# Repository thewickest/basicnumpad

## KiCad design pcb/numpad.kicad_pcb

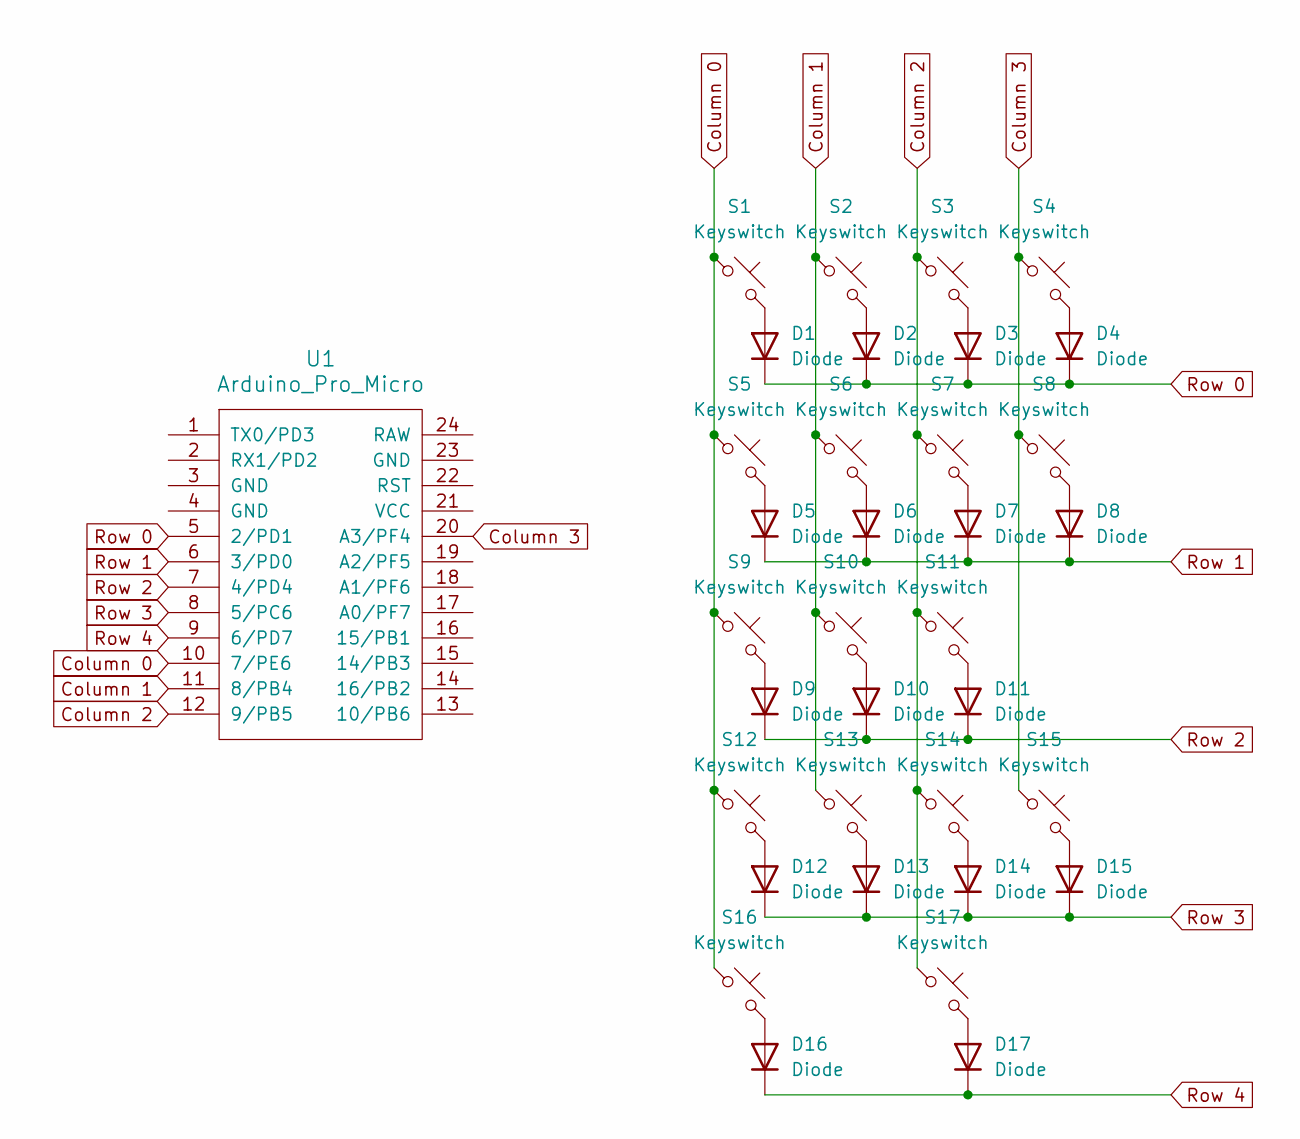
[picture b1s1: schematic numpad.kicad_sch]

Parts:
D1, D2, D3, D4, D5, D6, D7, D8, D9, D10, D11, D12, D13, D14, D15, D16, D17: Diode; Diode_DO-35
S1, S2, S3, S4, S5, S6, S7, S9, S10, S11, S12, S13, S14, S17: Keyswitch; MX_PCB_1.00u
S8, S15: Keyswitch; MX_PCB_2.00u_90deg
S16: Keyswitch; MX_PCB_2.00u
U1: Arduino_Pro_Micro

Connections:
Column 0: S1.1, S5.1, S9.1, S12.1, S16.1, U1.10 (7/PE6)
Column 1: S2.1, S6.1, S10.1, S13.1, U1.11 (8/PB4)
Column 2: S3.1, S7.1, S11.1, S14.1, S17.1, U1.12 (9/PB5)
Column 3: S4.1, S8.1, S15.1, U1.20 (A3/PF4)
unnamed: D1.2 (A), S1.2
unnamed: D2.2 (A), S2.2
unnamed: D3.2 (A), S3.2
unnamed: D4.2 (A), S4.2
unnamed: D5.2 (A), S5.2
unnamed: D6.2 (A), S6.2
unnamed: D7.2 (A), S7.2
unnamed: D8.2 (A), S8.2
unnamed: D9.2 (A), S9.2
unnamed: D10.2 (A), S10.2
unnamed: D11.2 (A), S11.2
unnamed: D12.2 (A), S12.2
unnamed: D13.2 (A), S13.2
unnamed: D14.2 (A), S14.2
unnamed: D15.2 (A), S15.2
unnamed: D16.2 (A), S16.2
unnamed: D17.2 (A), S17.2
Row 0: D1.1 (K), D2.1 (K), D3.1 (K), D4.1 (K), U1.5 (2/PD1)
Row 1: D5.1 (K), D6.1 (K), D7.1 (K), D8.1 (K), U1.6 (3/PD0)
Row 2: D9.1 (K), D10.1 (K), D11.1 (K), U1.7 (4/PD4)
Row 3: D12.1 (K), D13.1 (K), D14.1 (K), D15.1 (K), U1.8 (5/PC6)
Row 4: D16.1 (K), D17.1 (K), U1.9 (6/PD7)

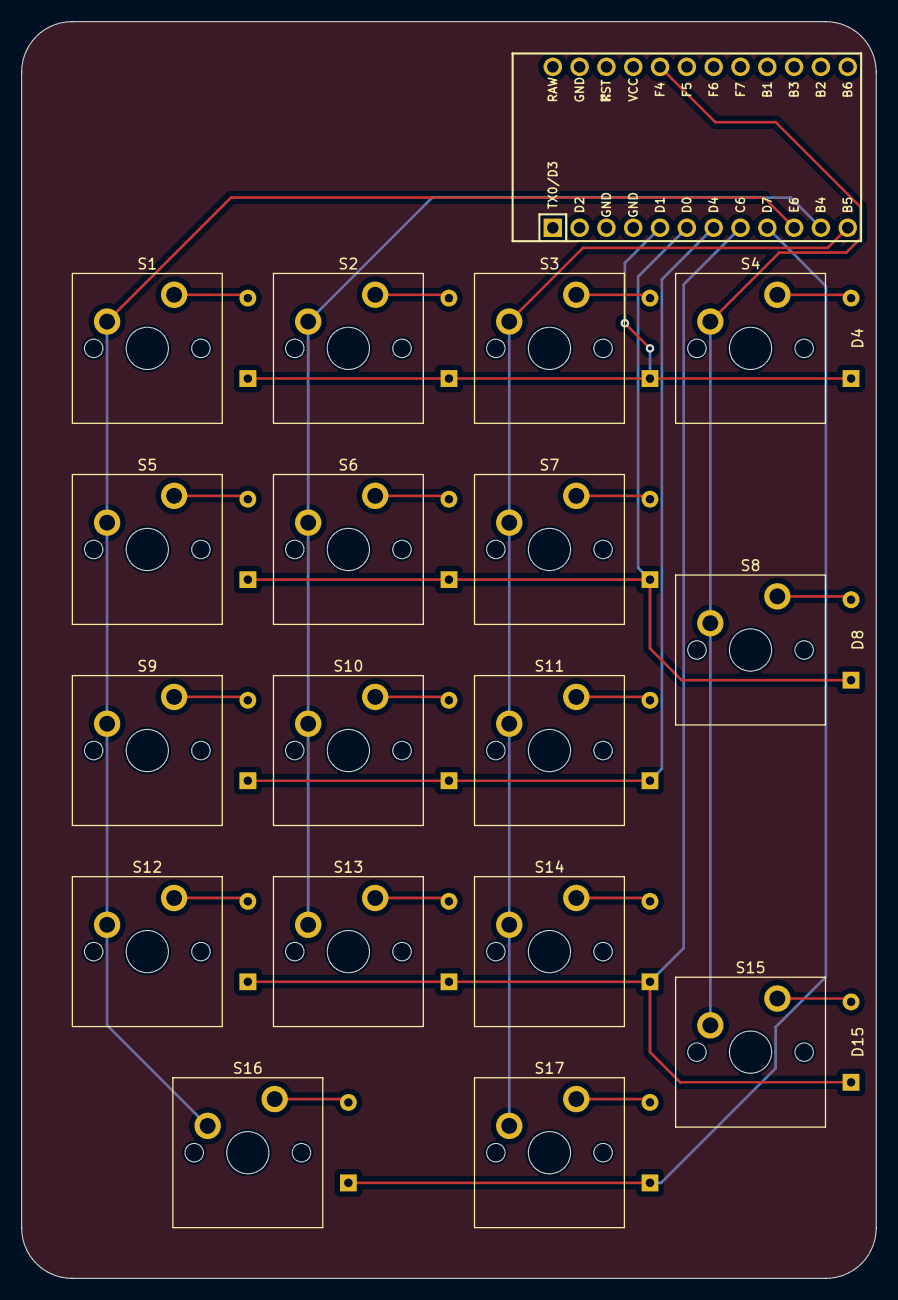
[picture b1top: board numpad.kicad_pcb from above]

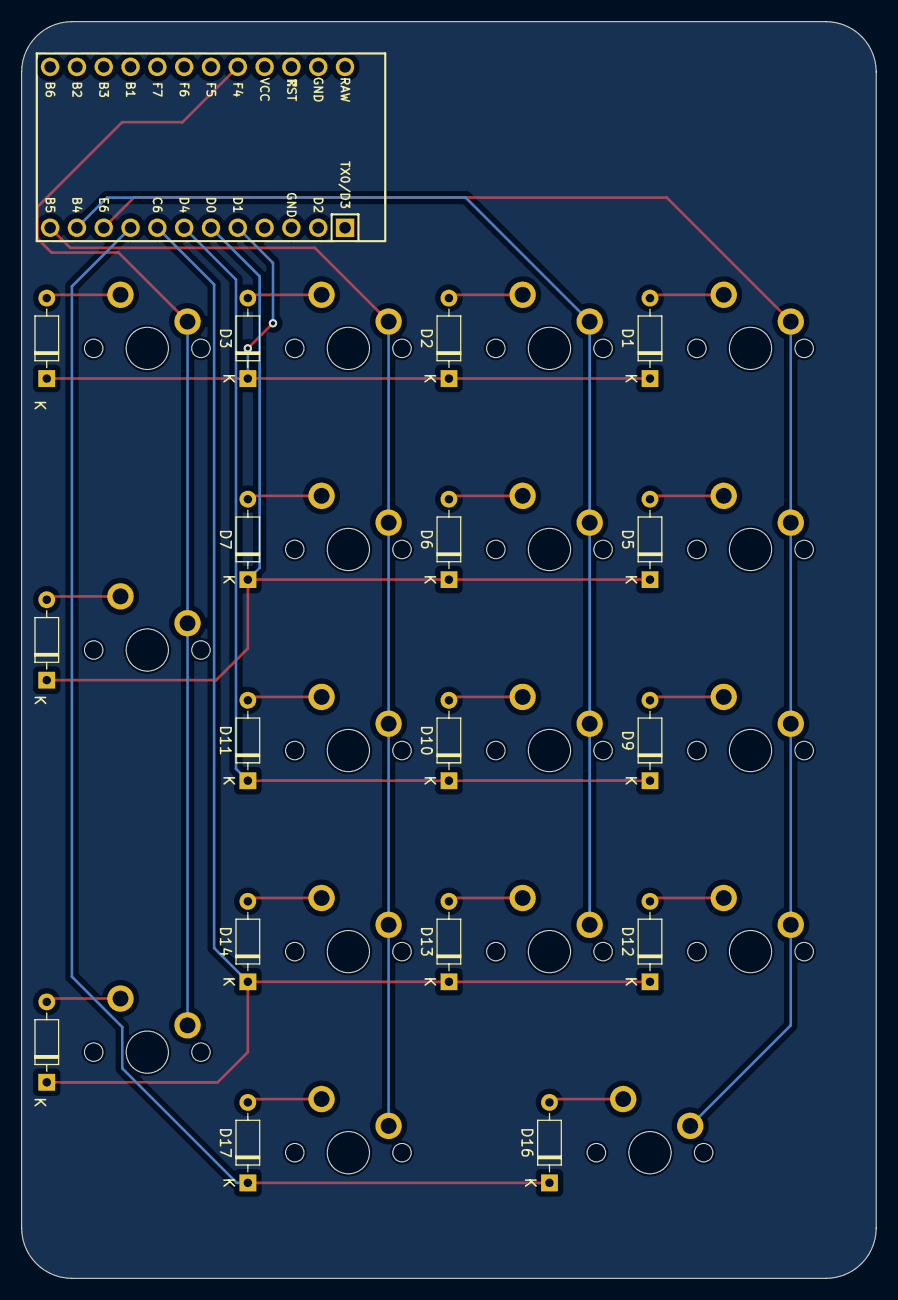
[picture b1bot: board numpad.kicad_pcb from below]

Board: 2 copper layers, 81.0 x 119.1 mm, 35 parts (17 on the bottom side), 26 nets.

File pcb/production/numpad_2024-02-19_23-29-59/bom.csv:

Designator,Footprint,Quantity,Value,LCSC Part #
"D1, D10, D11, D12, D13, D14, D15, D16, D17, D2, D3, D4, D5, D6, D7, D8, D9",Diode_DO-35,17,Diode,
"S1, S10, S11, S12, S13, S14, S17, S2, S3, S4, S5, S6, S7, S9",MX_PCB_1.00u,14,Keyswitch,
"S15, S8",MX_PCB_2.00u_90deg,2,Keyswitch,
S16,MX_PCB_2.00u,1,Keyswitch,
U1,Arduino_Pro_Micro,1,Arduino_Pro_Micro,

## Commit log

2025-01-29 Case updated with proper screw holes
2025-01-29 Proper Screw holes
2025-01-29 Custom Keymap for QMK
2025-01-29 Functions keys to remove App buttons
2025-01-31 Add Calculator to custom keymap
2025-01-31 New functionalities added to the keymap: Calculator, Notes, Spotify, VsCode, Fusion360, Github, Email and Calendar
2025-01-31 Some changes
2025-02-05 VIA Support
